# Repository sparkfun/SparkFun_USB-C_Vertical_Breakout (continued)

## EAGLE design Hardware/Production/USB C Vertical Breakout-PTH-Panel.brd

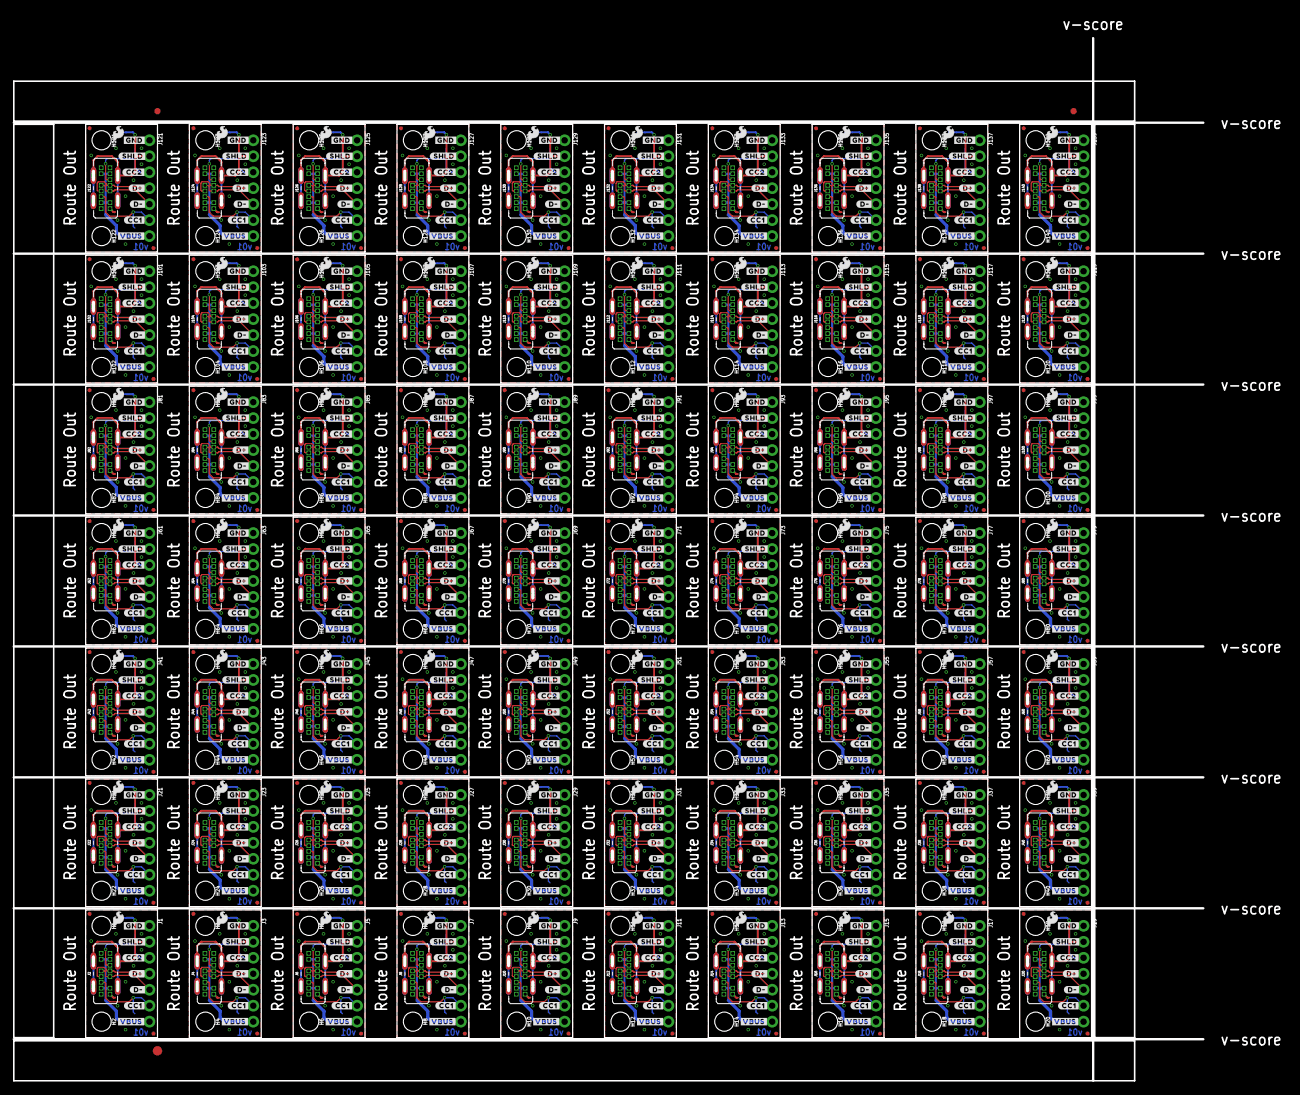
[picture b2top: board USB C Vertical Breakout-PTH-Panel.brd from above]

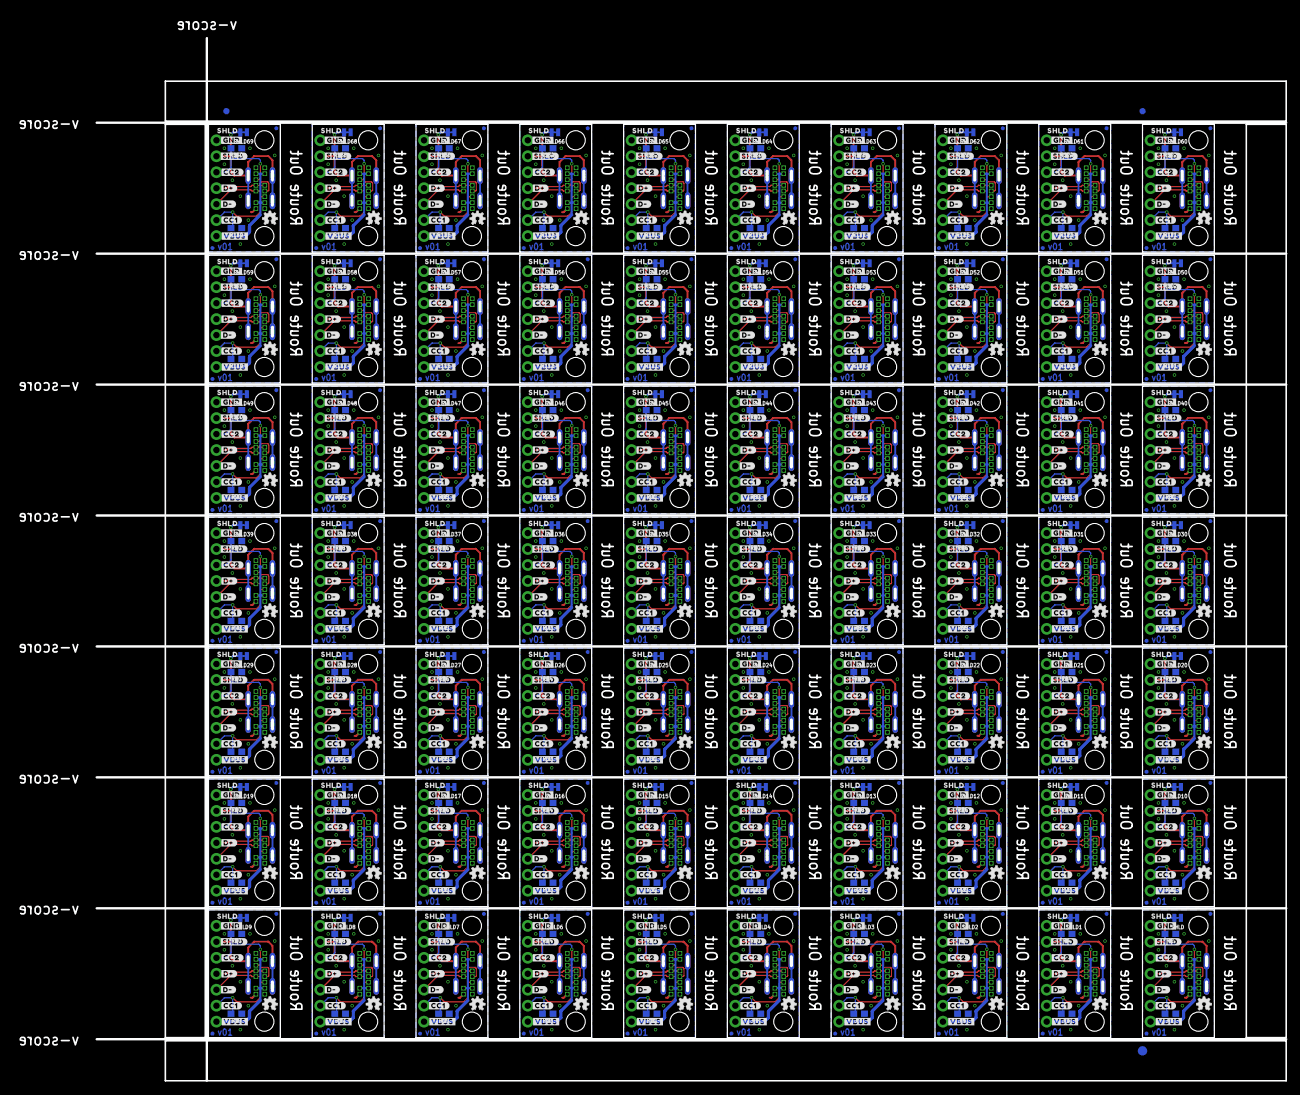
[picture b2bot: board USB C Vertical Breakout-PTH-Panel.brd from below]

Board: 2 copper layers, 189.2 x 165.9 mm, 2036 parts (983 on the bottom side), 490 nets.

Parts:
E$1, E$2, E$3, E$4: FIDUCIAL-1X2
E$5, E$6: FIDUCIAL-1.5X3
FD1, FD2, FD3, FD4, FD5, FD6, FD7, FD8, FD9, FD10, FD11, FD12, FD13, FD14, FD15, FD16, FD17, FD18, FD19, FD20, FD21, FD22, FD23, FD24, FD25, FD26, FD27, FD28, FD29, FD30, FD31, FD32, FD33, FD34, FD35, FD36, FD37, FD38, FD39, FD40, FD41, FD42, FD43, FD44, FD45, FD46, FD47, FD48, FD49, FD50, FD51, FD52, FD53, FD54, FD55, FD56, FD57, FD58, FD59, FD60, FD61, FD62, FD63, FD64, FD65, FD66, FD67, FD68, FD69, FD70, FD71, FD72, FD73, FD74, FD75, FD76, FD77, FD78, FD79, FD80, FD81, FD82, FD83, FD84, FD85, FD86, FD87, FD88, FD89, FD90, FD91, FD92, FD93, FD94, FD95, FD96, FD97, FD98, FD99, FD100, FD101, FD102, FD103, FD104, FD105, FD106, FD107, FD108, FD109, FD110, FD111, FD112, FD113, FD114, FD115, FD116, FD117, FD118, FD119, FD120, FD121, FD122, FD123, FD124, FD125, FD126, FD127, FD128, FD129, FD130, FD131, FD132, FD133, FD134, FD135, FD136, FD137, FD138, FD139, FD140, FD141, FD142, FD143, FD144, FD145, FD146, FD147, FD148, FD149, FD150, FD151, FD152, FD153, FD154, FD155, FD156, FD157, FD158, FD159, FD160, FD161, FD162, FD163, FD164, FD165, FD166, FD167, FD168, FD169, FD170, FD171, FD172, FD173, FD174, FD175, FD176, FD177, FD178, FD179, FD180, FD181, FD182, FD183, FD184, FD185, FD186, FD187, FD188, FD189, FD190, FD191, FD192, FD193, FD194, FD195, FD196, FD197, FD198, FD199, FD200, FD201, FD202, FD203, FD204, FD205, FD206, FD207, FD208, FD209, FD210, FD211, FD212, FD213, FD214, FD215, FD216, FD217, FD218, FD219, FD220, FD221, FD222, FD223, FD224, FD225, FD226, FD227, FD228, FD229, FD230, FD231, FD232, FD233, FD234, FD235, FD236, FD237, FD238, FD239, FD240, FD241, FD242, FD243, FD244, FD245, FD246, FD247, FD248, FD249, FD250, FD251, FD252, FD253, FD254, FD255, FD256, FD257, FD258, FD259, FD260, FD261, FD262, FD263, FD264, FD265, FD266, FD267, FD268, FD269, FD270, FD271, FD272, FD273, FD274, FD275, FD276, FD277, FD278, FD279, FD280: FIDUCIALUFIDUCIAL; FIDUCIAL-MICRO
H1, H2, H3, H4, H5, H6, H7, H8, H9, H10, H11, H12, H13, H14, H15, H16, H17, H18, H19, H20, H21, H22, H23, H24, H25, H26, H27, H28, H29, H30, H31, H32, H33, H34, H35, H36, H37, H38, H39, H40, H41, H42, H43, H44, H45, H46, H47, H48, H49, H50, H51, H52, H53, H54, H55, H56, H57, H58, H59, H60, H61, H62, H63, H64, H65, H66, H67, H68, H69, H70, H71, H72, H73, H74, H75, H76, H77, H78, H79, H80, H81, H82, H83, H84, H85, H86, H87, H88, H89, H90, H91, H92, H93, H94, H95, H96, H97, H98, H99, H100, H101, H102, H103, H104, H105, H106, H107, H108, H109, H110, H111, H112, H113, H114, H115, H116, H117, H118, H119, H120, H121, H122, H123, H124, H125, H126, H127, H128, H129, H130, H131, H132, H133, H134, H135, H136, H137, H138, H139, H140: STAND-OFFTIGHT; STAND-OFF-TIGHT
J1, J3, J5, J7, J9, J11, J13, J15, J17, J19, J21, J23, J25, J27, J29, J31, J33, J35, J37, J39, J41, J43, J45, J47, J49, J51, J53, J55, J57, J59, J61, J63, J65, J67, J69, J71, J73, J75, J77, J79, J81, J83, J85, J87, J89, J91, J93, J95, J97, J99, J101, J103, J105, J107, J109, J111, J113, J115, J117, J119, J121, J123, J125, J127, J129, J131, J133, J135, J137, J139: 1X07_NO_SILK
J2, J4, J6, J8, J10, J12, J14, J16, J18, J20, J22, J24, J26, J28, J30, J32, J34, J36, J38, J40, J42, J44, J46, J48, J50, J52, J54, J56, J58, J60, J62, J64, J66, J68, J70, J72, J74, J76, J78, J80, J82, J84, J86, J88, J90, J92, J94, J96, J98, J100, J102, J104, J106, J108, J110, J112, J114, J116, J118, J120, J122, J124, J126, J128, J130, J132, J134, J136, J138, J140: USB-C-8P-2LAYER-VERTICAL-PTH
LOGO1, LOGO5, LOGO8, LOGO11, LOGO14, LOGO17, LOGO20, LOGO23, LOGO26, LOGO29, LOGO32, LOGO35, LOGO38, LOGO41, LOGO44, LOGO47, LOGO50, LOGO53, LOGO56, LOGO59, LOGO62, LOGO65, LOGO68, LOGO71, LOGO74, LOGO77, LOGO80, LOGO83, LOGO86, LOGO89, LOGO92, LOGO95, LOGO98, LOGO101, LOGO104, LOGO107, LOGO110, LOGO113, LOGO116, LOGO119, LOGO122, LOGO125, LOGO128, LOGO131, LOGO134, LOGO137, LOGO140, LOGO143, LOGO146, LOGO149, LOGO152, LOGO155, LOGO158, LOGO161, LOGO164, LOGO167, LOGO170, LOGO173, LOGO176, LOGO179, LOGO182, LOGO185, LOGO188, LOGO191, LOGO194, LOGO197, LOGO200, LOGO203, LOGO206, LOGO209: SFE_LOGO_NAME_FLAMEBLANK; BLANK
LOGO2, LOGO4, LOGO7, LOGO10, LOGO13, LOGO16, LOGO19, LOGO22, LOGO25, LOGO28, LOGO31, LOGO34, LOGO37, LOGO40, LOGO43, LOGO46, LOGO49, LOGO52, LOGO55, LOGO58, LOGO61, LOGO64, LOGO67, LOGO70, LOGO73, LOGO76, LOGO79, LOGO82, LOGO85, LOGO88, LOGO91, LOGO94, LOGO97, LOGO100, LOGO103, LOGO106, LOGO109, LOGO112, LOGO115, LOGO118, LOGO121, LOGO124, LOGO127, LOGO130, LOGO133, LOGO136, LOGO139, LOGO142, LOGO145, LOGO148, LOGO151, LOGO154, LOGO157, LOGO160, LOGO163, LOGO166, LOGO169, LOGO172, LOGO175, LOGO178, LOGO181, LOGO184, LOGO187, LOGO190, LOGO193, LOGO196, LOGO199, LOGO202, LOGO205, LOGO208: OSHW-LOGOMINI; OSHW-LOGO-MINI
LOGO3, LOGO6, LOGO9, LOGO12, LOGO15, LOGO18, LOGO21, LOGO24, LOGO27, LOGO30, LOGO33, LOGO36, LOGO39, LOGO42, LOGO45, LOGO48, LOGO51, LOGO54, LOGO57, LOGO60, LOGO63, LOGO66, LOGO69, LOGO72, LOGO75, LOGO78, LOGO81, LOGO84, LOGO87, LOGO90, LOGO93, LOGO96, LOGO99, LOGO102, LOGO105, LOGO108, LOGO111, LOGO114, LOGO117, LOGO120, LOGO123, LOGO126, LOGO129, LOGO132, LOGO135, LOGO138, LOGO141, LOGO144, LOGO147, LOGO150, LOGO153, LOGO156, LOGO159, LOGO162, LOGO165, LOGO168, LOGO171, LOGO174, LOGO177, LOGO180, LOGO183, LOGO186, LOGO189, LOGO192, LOGO195, LOGO198, LOGO201, LOGO204, LOGO207, LOGO210: SFE_LOGO_FLAME.1_INCH; SFE_LOGO_FLAME_.1
R1, R2, R3, R4, R5, R6, R7, R8, R9, R10, R11, R12, R13, R14, R15, R16, R17, R18, R19, R20, R21, R22, R23, R24, R25, R26, R27, R28, R29, R30, R31, R32, R33, R34, R35, R36, R37, R38, R39, R40, R41, R42, R43, R44, R45, R46, R47, R48, R49, R50, R51, R52, R53, R54, R55, R56, R57, R58, R59, R60, R61, R62, R63, R64, R65, R66, R67, R68, R69, R70, R71, R72, R73, R74, R75, R76, R77, R78, R79, R80, R81, R82, R83, R84, R85, R86, R87, R88, R89, R90, R91, R92, R93, R94, R95, R96, R97, R98, R99, R100, R101, R102, R103, R104, R105, R106, R107, R108, R109, R110, R111, R112, R113, R114, R115, R116, R117, R118, R119, R120, R121, R122, R123, R124, R125, R126, R127, R128, R129, R130, R131, R132, R133, R134, R135, R136, R137, R138, R139, R140: 5.1k; 0603
SHLD, SHLD1, SHLD2, SHLD3, SHLD4, SHLD5, SHLD6, SHLD7, SHLD8, SHLD9, SHLD10, SHLD11, SHLD12, SHLD13, SHLD14, SHLD15, SHLD16, SHLD17, SHLD18, SHLD19, SHLD20, SHLD21, SHLD22, SHLD23, SHLD24, SHLD25, SHLD26, SHLD27, SHLD28, SHLD29, SHLD30, SHLD31, SHLD32, SHLD33, SHLD34, SHLD35, SHLD36, SHLD37, SHLD38, SHLD39, SHLD40, SHLD41, SHLD42, SHLD43, SHLD44, SHLD45, SHLD46, SHLD47, SHLD48, SHLD49, SHLD50, SHLD51, SHLD52, SHLD53, SHLD54, SHLD55, SHLD56, SHLD57, SHLD58, SHLD59, SHLD60, SHLD61, SHLD62, SHLD63, SHLD64, SHLD65, SHLD66, SHLD67, SHLD68, SHLD69: SHLD; SMT-JUMPER_2_NC_TRACE_NO-SILK
U$1, U$30, U$45, U$60, U$75, U$90, U$105, U$120, U$135, U$150, U$165, U$180, U$195, U$210, U$225, U$240, U$255, U$270, U$285, U$300, U$315, U$330, U$345, U$360, U$375, U$390, U$405, U$420, U$435, U$450, U$465, U$480, U$495, U$510, U$525, U$540, U$555, U$570, U$585, U$600, U$615, U$630, U$645, U$660, U$675, U$690, U$705, U$720, U$735, U$750, U$765, U$780, U$795, U$810, U$825, U$840, U$855, U$870, U$885, U$900, U$915, U$930, U$945, U$960, U$975, U$990, U$1005, U$1020, U$1035, U$1050: SHLD0
U$2, U$16, U$31, U$46, U$61, U$76, U$91, U$106, U$121, U$136, U$151, U$166, U$181, U$196, U$211, U$226, U$241, U$256, U$271, U$286, U$301, U$316, U$331, U$346, U$361, U$376, U$391, U$406, U$421, U$436, U$451, U$466, U$481, U$496, U$511, U$526, U$541, U$556, U$571, U$586, U$601, U$616, U$631, U$646, U$661, U$676, U$691, U$706, U$721, U$736, U$751, U$766, U$781, U$796, U$811, U$826, U$841, U$856, U$871, U$886, U$901, U$916, U$931, U$946, U$961, U$976, U$991, U$1006, U$1021, U$1036: #CC2#0
U$3, U$4, U$32, U$47, U$62, U$77, U$92, U$107, U$122, U$137, U$152, U$167, U$182, U$197, U$212, U$227, U$242, U$257, U$272, U$287, U$302, U$317, U$332, U$347, U$362, U$377, U$392, U$407, U$422, U$437, U$452, U$467, U$482, U$497, U$512, U$527, U$542, U$557, U$572, U$587, U$602, U$617, U$632, U$647, U$662, U$677, U$692, U$707, U$722, U$737, U$752, U$767, U$782, U$797, U$812, U$827, U$842, U$857, U$872, U$887, U$902, U$917, U$932, U$947, U$962, U$977, U$992, U$1007, U$1022, U$1037: #D##3
U$5, U$7, U$33, U$48, U$63, U$78, U$93, U$108, U$123, U$138, U$153, U$168, U$183, U$198, U$213, U$228, U$243, U$258, U$273, U$288, U$303, U$318, U$333, U$348, U$363, U$378, U$393, U$408, U$423, U$438, U$453, U$468, U$483, U$498, U$513, U$528, U$543, U$558, U$573, U$588, U$603, U$618, U$633, U$648, U$663, U$678, U$693, U$708, U$723, U$738, U$753, U$768, U$783, U$798, U$813, U$828, U$843, U$858, U$873, U$888, U$903, U$918, U$933, U$948, U$963, U$978, U$993, U$1008, U$1023, U$1038: #D##4
U$6, U$17, U$34, U$49, U$64, U$79, U$94, U$109, U$124, U$139, U$154, U$169, U$184, U$199, U$214, U$229, U$244, U$259, U$274, U$289, U$304, U$319, U$334, U$349, U$364, U$379, U$394, U$409, U$424, U$439, U$454, U$469, U$484, U$499, U$514, U$529, U$544, U$559, U$574, U$589, U$604, U$619, U$634, U$649, U$664, U$679, U$694, U$709, U$724, U$739, U$754, U$769, U$784, U$799, U$814, U$829, U$844, U$859, U$874, U$889, U$904, U$919, U$934, U$949, U$964, U$979, U$994, U$1009, U$1024, U$1039: #CC1#5
U$8, U$18, U$35, U$50, U$65, U$80, U$95, U$110, U$125, U$140, U$155, U$170, U$185, U$200, U$215, U$230, U$245, U$260, U$275, U$290, U$305, U$320, U$335, U$350, U$365, U$380, U$395, U$410, U$425, U$440, U$455, U$470, U$485, U$500, U$515, U$530, U$545, U$560, U$575, U$590, U$605, U$620, U$635, U$650, U$665, U$680, U$695, U$710, U$725, U$740, U$755, U$770, U$785, U$800, U$815, U$830, U$845, U$860, U$875, U$890, U$905, U$920, U$935, U$950, U$965, U$980, U$995, U$1010, U$1025, U$1040: #SHLD#5
U$9, U$10, U$13, U$21, U$36, U$39, U$51, U$54, U$66, U$69, U$81, U$84, U$96, U$99, U$111, U$114, U$126, U$129, U$141, U$144, U$156, U$159, U$171, U$174, U$186, U$189, U$201, U$204, U$216, U$219, U$231, U$234, U$246, U$249, U$261, U$264, U$276, U$279, U$291, U$294, U$306, U$309, U$321, U$324, U$336, U$339, U$351, U$354, U$366, U$369, U$381, U$384, U$396, U$399, U$411, U$414, U$426, U$429, U$441, U$444, U$456, U$459, U$471, U$474, U$486, U$489, U$501, U$504, U$516, U$519, U$531, U$534, U$546, U$549, U$561, U$564, U$576, U$579, U$591, U$594, U$606, U$609, U$621, U$624, U$636, U$639, U$651, U$654, U$666, U$669, U$681, U$684, U$696, U$699, U$711, U$714, U$726, U$729, U$741, U$744, U$756, U$759, U$771, U$774, U$786, U$789, U$801, U$804, U$816, U$819, U$831, U$834, U$846, U$849, U$861, U$864, U$876, U$879, U$891, U$894, U$906, U$909, U$921, U$924, U$936, U$939, U$951, U$954, U$966, U$969, U$981, U$984, U$996, U$999, U$1011, U$1014, U$1026, U$1029, U$1041, U$1044: #GND#6
U$11, U$12, U$19, U$20, U$37, U$38, U$52, U$53, U$67, U$68, U$82, U$83, U$97, U$98, U$112, U$113, U$127, U$128, U$142, U$143, U$157, U$158, U$172, U$173, U$187, U$188, U$202, U$203, U$217, U$218, U$232, U$233, U$247, U$248, U$262, U$263, U$277, U$278, U$292, U$293, U$307, U$308, U$322, U$323, U$337, U$338, U$352, U$353, U$367, U$368, U$382, U$383, U$397, U$398, U$412, U$413, U$427, U$428, U$442, U$443, U$457, U$458, U$472, U$473, U$487, U$488, U$502, U$503, U$517, U$518, U$532, U$533, U$547, U$548, U$562, U$563, U$577, U$578, U$592, U$593, U$607, U$608, U$622, U$623, U$637, U$638, U$652, U$653, U$667, U$668, U$682, U$683, U$697, U$698, U$712, U$713, U$727, U$728, U$742, U$743, U$757, U$758, U$772, U$773, U$787, U$788, U$802, U$803, U$817, U$818, U$832, U$833, U$847, U$848, U$862, U$863, U$877, U$878, U$892, U$893, U$907, U$908, U$922, U$923, U$937, U$938, U$952, U$953, U$967, U$968, U$982, U$983, U$997, U$998, U$1012, U$1013, U$1027, U$1028, U$1042, U$1043: #VBUS#7
U$14, U$22, U$40, U$55, U$70, U$85, U$100, U$115, U$130, U$145, U$160, U$175, U$190, U$205, U$220, U$235, U$250, U$265, U$280, U$295, U$310, U$325, U$340, U$355, U$370, U$385, U$400, U$415, U$430, U$445, U$460, U$475, U$490, U$505, U$520, U$535, U$550, U$565, U$580, U$595, U$610, U$625, U$640, U$655, U$670, U$685, U$700, U$715, U$730, U$745, U$760, U$775, U$790, U$805, U$820, U$835, U$850, U$865, U$880, U$895, U$910, U$925, U$940, U$955, U$970, U$985, U$1000, U$1015, U$1030, U$1045: #SHLD#8
U$15, U$23, U$41, U$56, U$71, U$86, U$101, U$116, U$131, U$146, U$161, U$176, U$191, U$206, U$221, U$236, U$251, U$266, U$281, U$296, U$311, U$326, U$341, U$356, U$371, U$386, U$401, U$416, U$431, U$446, U$461, U$476, U$491, U$506, U$521, U$536, U$551, U$566, U$581, U$596, U$611, U$626, U$641, U$656, U$671, U$686, U$701, U$716, U$731, U$746, U$761, U$776, U$791, U$806, U$821, U$836, U$851, U$866, U$881, U$896, U$911, U$926, U$941, U$956, U$971, U$986, U$1001, U$1016, U$1031, U$1046: #CC2#9
U$24, U$27, U$42, U$57, U$72, U$87, U$102, U$117, U$132, U$147, U$162, U$177, U$192, U$207, U$222, U$237, U$252, U$267, U$282, U$297, U$312, U$327, U$342, U$357, U$372, U$387, U$402, U$417, U$432, U$447, U$462, U$477, U$492, U$507, U$522, U$537, U$552, U$567, U$582, U$597, U$612, U$627, U$642, U$657, U$672, U$687, U$702, U$717, U$732, U$747, U$762, U$777, U$792, U$807, U$822, U$837, U$852, U$867, U$882, U$897, U$912, U$927, U$942, U$957, U$972, U$987, U$1002, U$1017, U$1032, U$1047: #D##9
U$25, U$28, U$43, U$58, U$73, U$88, U$103, U$118, U$133, U$148, U$163, U$178, U$193, U$208, U$223, U$238, U$253, U$268, U$283, U$298, U$313, U$328, U$343, U$358, U$373, U$388, U$403, U$418, U$433, U$448, U$463, U$478, U$493, U$508, U$523, U$538, U$553, U$568, U$583, U$598, U$613, U$628, U$643, U$658, U$673, U$688, U$703, U$718, U$733, U$748, U$763, U$778, U$793, U$808, U$823, U$838, U$853, U$868, U$883, U$898, U$913, U$928, U$943, U$958, U$973, U$988, U$1003, U$1018, U$1033, U$1048: #D##10
U$26, U$29, U$44, U$59, U$74, U$89, U$104, U$119, U$134, U$149, U$164, U$179, U$194, U$209, U$224, U$239, U$254, U$269, U$284, U$299, U$314, U$329, U$344, U$359, U$374, U$389, U$404, U$419, U$434, U$449, U$464, U$479, U$494, U$509, U$524, U$539, U$554, U$569, U$584, U$599, U$614, U$629, U$644, U$659, U$674, U$689, U$704, U$719, U$734, U$749, U$764, U$779, U$794, U$809, U$824, U$839, U$854, U$869, U$884, U$899, U$914, U$929, U$944, U$959, U$974, U$989, U$1004, U$1019, U$1034, U$1049: #CC1#11

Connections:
CC1: J1.6, J2.A5, R1.2
CC2: J1.3, J2.B5, R2.2
CC3: J3.6, J4.A5, R3.2
CC4: J3.3, J4.B5, R4.2
CC5: J5.6, J6.A5, R5.2
CC6: J5.3, J6.B5, R6.2
CC7: J7.6, J8.A5, R7.2
CC8: J7.3, J8.B5, R8.2
CC9: J9.6, J10.A5, R9.2
CC10: J9.3, J10.B5, R10.2
CC11: J11.6, J12.A5, R11.2
CC12: J11.3, J12.B5, R12.2
CC13: J13.6, J14.A5, R13.2
CC14: J13.3, J14.B5, R14.2
CC15: J15.6, J16.A5, R15.2
CC16: J15.3, J16.B5, R16.2
CC17: J17.6, J18.A5, R17.2
CC18: J17.3, J18.B5, R18.2
CC19: J19.6, J20.A5, R19.2
CC20: J19.3, J20.B5, R20.2
CC21: J21.6, J22.A5, R21.2
CC22: J21.3, J22.B5, R22.2
CC23: J23.6, J24.A5, R23.2
CC24: J23.3, J24.B5, R24.2
CC25: J25.6, J26.A5, R25.2
CC26: J25.3, J26.B5, R26.2
CC27: J27.6, J28.A5, R27.2
CC28: J27.3, J28.B5, R28.2
CC29: J29.6, J30.A5, R29.2
CC30: J29.3, J30.B5, R30.2
CC31: J31.6, J32.A5, R31.2
CC32: J31.3, J32.B5, R32.2
CC33: J33.6, J34.A5, R33.2
CC34: J33.3, J34.B5, R34.2
CC35: J35.6, J36.A5, R35.2
CC36: J35.3, J36.B5, R36.2
CC37: J37.6, J38.A5, R37.2
CC38: J37.3, J38.B5, R38.2
CC39: J39.6, J40.A5, R39.2
CC40: J39.3, J40.B5, R40.2
CC41: J41.6, J42.A5, R41.2
CC42: J41.3, J42.B5, R42.2
CC43: J43.6, J44.A5, R43.2
CC44: J43.3, J44.B5, R44.2
CC45: J45.6, J46.A5, R45.2
CC46: J45.3, J46.B5, R46.2
CC47: J47.6, J48.A5, R47.2
CC48: J47.3, J48.B5, R48.2
CC49: J49.6, J50.A5, R49.2
CC50: J49.3, J50.B5, R50.2
CC51: J51.6, J52.A5, R51.2
CC52: J51.3, J52.B5, R52.2
CC53: J53.6, J54.A5, R53.2
CC54: J53.3, J54.B5, R54.2
CC55: J55.6, J56.A5, R55.2
CC56: J55.3, J56.B5, R56.2
CC57: J57.6, J58.A5, R57.2
CC58: J57.3, J58.B5, R58.2
CC59: J59.6, J60.A5, R59.2
CC60: J59.3, J60.B5, R60.2
CC61: J61.6, J62.A5, R61.2
CC62: J61.3, J62.B5, R62.2
CC63: J63.6, J64.A5, R63.2
CC64: J63.3, J64.B5, R64.2
CC65: J65.6, J66.A5, R65.2
CC66: J65.3, J66.B5, R66.2
CC67: J67.6, J68.A5, R67.2
CC68: J67.3, J68.B5, R68.2
CC69: J69.6, J70.A5, R69.2
CC70: J69.3, J70.B5, R70.2
CC71: J71.6, J72.A5, R71.2
CC72: J71.3, J72.B5, R72.2
CC73: J73.6, J74.A5, R73.2
CC74: J73.3, J74.B5, R74.2
CC75: J75.6, J76.A5, R75.2
CC76: J75.3, J76.B5, R76.2
CC77: J77.6, J78.A5, R77.2
CC78: J77.3, J78.B5, R78.2
CC79: J79.6, J80.A5, R79.2
CC80: J79.3, J80.B5, R80.2
CC81: J81.6, J82.A5, R81.2
CC82: J81.3, J82.B5, R82.2
CC83: J83.6, J84.A5, R83.2
CC84: J83.3, J84.B5, R84.2
CC85: J85.6, J86.A5, R85.2
CC86: J85.3, J86.B5, R86.2
CC87: J87.6, J88.A5, R87.2
CC88: J87.3, J88.B5, R88.2
CC89: J89.6, J90.A5, R89.2
CC90: J89.3, J90.B5, R90.2
CC91: J91.6, J92.A5, R91.2
CC92: J91.3, J92.B5, R92.2
CC93: J93.6, J94.A5, R93.2
CC94: J93.3, J94.B5, R94.2
CC95: J95.6, J96.A5, R95.2
CC96: J95.3, J96.B5, R96.2
CC97: J97.6, J98.A5, R97.2
CC98: J97.3, J98.B5, R98.2
CC99: J99.6, J100.A5, R99.2
CC100: J99.3, J100.B5, R100.2
CC101: J101.6, J102.A5, R101.2
CC102: J101.3, J102.B5, R102.2
CC103: J103.6, J104.A5, R103.2
CC104: J103.3, J104.B5, R104.2
CC105: J105.6, J106.A5, R105.2
CC106: J105.3, J106.B5, R106.2
CC107: J107.6, J108.A5, R107.2
CC108: J107.3, J108.B5, R108.2
CC109: J109.6, J110.A5, R109.2
CC110: J109.3, J110.B5, R110.2
CC111: J111.6, J112.A5, R111.2
CC112: J111.3, J112.B5, R112.2
CC113: J113.6, J114.A5, R113.2
CC114: J113.3, J114.B5, R114.2
CC115: J115.6, J116.A5, R115.2
CC116: J115.3, J116.B5, R116.2
CC117: J117.6, J118.A5, R117.2
CC118: J117.3, J118.B5, R118.2
CC119: J119.6, J120.A5, R119.2
CC120: J119.3, J120.B5, R120.2
CC121: J121.6, J122.A5, R121.2
CC122: J121.3, J122.B5, R122.2
CC123: J123.6, J124.A5, R123.2
CC124: J123.3, J124.B5, R124.2
CC125: J125.6, J126.A5, R125.2
CC126: J125.3, J126.B5, R126.2
CC127: J127.6, J128.A5, R127.2
CC128: J127.3, J128.B5, R128.2
CC129: J129.6, J130.A5, R129.2
CC130: J129.3, J130.B5, R130.2
CC131: J131.6, J132.A5, R131.2
CC132: J131.3, J132.B5, R132.2
CC133: J133.6, J134.A5, R133.2
CC134: J133.3, J134.B5, R134.2
CC135: J135.6, J136.A5, R135.2
CC136: J135.3, J136.B5, R136.2
CC137: J137.6, J138.A5, R137.2
CC138: J137.3, J138.B5, R138.2
CC139: J139.6, J140.A5, R139.2
CC140: J139.3, J140.B5, R140.2
D+: J1.4, J2.A6, J2.B6
D+1: J3.4, J4.A6, J4.B6
D+2: J5.4, J6.A6, J6.B6
D+3: J7.4, J8.A6, J8.B6
D+4: J9.4, J10.A6, J10.B6
D+5: J11.4, J12.A6, J12.B6
D+6: J13.4, J14.A6, J14.B6
D+7: J15.4, J16.A6, J16.B6
D+8: J17.4, J18.A6, J18.B6
D+9: J19.4, J20.A6, J20.B6
D+10: J21.4, J22.A6, J22.B6
D+11: J23.4, J24.A6, J24.B6
D+12: J25.4, J26.A6, J26.B6
D+13: J27.4, J28.A6, J28.B6
D+14: J29.4, J30.A6, J30.B6
D+15: J31.4, J32.A6, J32.B6
D+16: J33.4, J34.A6, J34.B6
D+17: J35.4, J36.A6, J36.B6
D+18: J37.4, J38.A6, J38.B6
D+19: J39.4, J40.A6, J40.B6
D+20: J41.4, J42.A6, J42.B6
D+21: J43.4, J44.A6, J44.B6
D+22: J45.4, J46.A6, J46.B6
D+23: J47.4, J48.A6, J48.B6
D+24: J49.4, J50.A6, J50.B6
D+25: J51.4, J52.A6, J52.B6
D+26: J53.4, J54.A6, J54.B6
D+27: J55.4, J56.A6, J56.B6
D+28: J57.4, J58.A6, J58.B6
D+29: J59.4, J60.A6, J60.B6
D+30: J61.4, J62.A6, J62.B6
D+31: J63.4, J64.A6, J64.B6
D+32: J65.4, J66.A6, J66.B6
D+33: J67.4, J68.A6, J68.B6
D+34: J69.4, J70.A6, J70.B6
D+35: J71.4, J72.A6, J72.B6
D+36: J73.4, J74.A6, J74.B6
D+37: J75.4, J76.A6, J76.B6
D+38: J77.4, J78.A6, J78.B6
D+39: J79.4, J80.A6, J80.B6
D+40: J81.4, J82.A6, J82.B6
D+41: J83.4, J84.A6, J84.B6
D+42: J85.4, J86.A6, J86.B6
D+43: J87.4, J88.A6, J88.B6
D+44: J89.4, J90.A6, J90.B6
D+45: J91.4, J92.A6, J92.B6
D+46: J93.4, J94.A6, J94.B6
D+47: J95.4, J96.A6, J96.B6
D+48: J97.4, J98.A6, J98.B6
D+49: J99.4, J100.A6, J100.B6
D+50: J101.4, J102.A6, J102.B6
D+51: J103.4, J104.A6, J104.B6
D+52: J105.4, J106.A6, J106.B6
D+53: J107.4, J108.A6, J108.B6
D+54: J109.4, J110.A6, J110.B6
D+55: J111.4, J112.A6, J112.B6
D+56: J113.4, J114.A6, J114.B6
D+57: J115.4, J116.A6, J116.B6
D+58: J117.4, J118.A6, J118.B6
D+59: J119.4, J120.A6, J120.B6
D+60: J121.4, J122.A6, J122.B6
D+61: J123.4, J124.A6, J124.B6
D+62: J125.4, J126.A6, J126.B6
D+63: J127.4, J128.A6, J128.B6
D+64: J129.4, J130.A6, J130.B6
D+65: J131.4, J132.A6, J132.B6
D+66: J133.4, J134.A6, J134.B6
D+67: J135.4, J136.A6, J136.B6
D+68: J137.4, J138.A6, J138.B6
D+69: J139.4, J140.A6, J140.B6
D-: J1.5, J2.A7, J2.B7
D-1: J3.5, J4.A7, J4.B7
D-2: J5.5, J6.A7, J6.B7
D-3: J7.5, J8.A7, J8.B7
D-4: J9.5, J10.A7, J10.B7
D-5: J11.5, J12.A7, J12.B7
D-6: J13.5, J14.A7, J14.B7
D-7: J15.5, J16.A7, J16.B7
D-8: J17.5, J18.A7, J18.B7
D-9: J19.5, J20.A7, J20.B7
D-10: J21.5, J22.A7, J22.B7
D-11: J23.5, J24.A7, J24.B7
D-12: J25.5, J26.A7, J26.B7
D-13: J27.5, J28.A7, J28.B7
D-14: J29.5, J30.A7, J30.B7
D-15: J31.5, J32.A7, J32.B7
D-16: J33.5, J34.A7, J34.B7
D-17: J35.5, J36.A7, J36.B7
D-18: J37.5, J38.A7, J38.B7
D-19: J39.5, J40.A7, J40.B7
D-20: J41.5, J42.A7, J42.B7
D-21: J43.5, J44.A7, J44.B7
D-22: J45.5, J46.A7, J46.B7
D-23: J47.5, J48.A7, J48.B7
D-24: J49.5, J50.A7, J50.B7
D-25: J51.5, J52.A7, J52.B7
D-26: J53.5, J54.A7, J54.B7
D-27: J55.5, J56.A7, J56.B7
D-28: J57.5, J58.A7, J58.B7
D-29: J59.5, J60.A7, J60.B7
D-30: J61.5, J62.A7, J62.B7
D-31: J63.5, J64.A7, J64.B7
D-32: J65.5, J66.A7, J66.B7
D-33: J67.5, J68.A7, J68.B7
D-34: J69.5, J70.A7, J70.B7
D-35: J71.5, J72.A7, J72.B7
D-36: J73.5, J74.A7, J74.B7
D-37: J75.5, J76.A7, J76.B7
D-38: J77.5, J78.A7, J78.B7
D-39: J79.5, J80.A7, J80.B7
D-40: J81.5, J82.A7, J82.B7
D-41: J83.5, J84.A7, J84.B7
D-42: J85.5, J86.A7, J86.B7
D-43: J87.5, J88.A7, J88.B7
D-44: J89.5, J90.A7, J90.B7
D-45: J91.5, J92.A7, J92.B7
D-46: J93.5, J94.A7, J94.B7
D-47: J95.5, J96.A7, J96.B7
D-48: J97.5, J98.A7, J98.B7
D-49: J99.5, J100.A7, J100.B7
D-50: J101.5, J102.A7, J102.B7
D-51: J103.5, J104.A7, J104.B7
D-52: J105.5, J106.A7, J106.B7
D-53: J107.5, J108.A7, J108.B7
D-54: J109.5, J110.A7, J110.B7
D-55: J111.5, J112.A7, J112.B7
D-56: J113.5, J114.A7, J114.B7
D-57: J115.5, J116.A7, J116.B7
D-58: J117.5, J118.A7, J118.B7
D-59: J119.5, J120.A7, J120.B7
D-60: J121.5, J122.A7, J122.B7
D-61: J123.5, J124.A7, J124.B7
D-62: J125.5, J126.A7, J126.B7
D-63: J127.5, J128.A7, J128.B7
D-64: J129.5, J130.A7, J130.B7
D-65: J131.5, J132.A7, J132.B7
D-66: J133.5, J134.A7, J134.B7
D-67: J135.5, J136.A7, J136.B7
D-68: J137.5, J138.A7, J138.B7
D-69: J139.5, J140.A7, J140.B7
GND: J1.1, J2.A1, J2.A12, J2.B1, J2.B12, R1.1, R2.1, SHLD.1
GND1: J3.1, J4.A1, J4.A12, J4.B1, J4.B12, R3.1, R4.1, SHLD1.1
GND2: J5.1, J6.A1, J6.A12, J6.B1, J6.B12, R5.1, R6.1, SHLD2.1
GND3: J7.1, J8.A1, J8.A12, J8.B1, J8.B12, R7.1, R8.1, SHLD3.1
GND4: J9.1, J10.A1, J10.A12, J10.B1, J10.B12, R9.1, R10.1, SHLD4.1
GND5: J11.1, J12.A1, J12.A12, J12.B1, J12.B12, R11.1, R12.1, SHLD5.1
GND6: J13.1, J14.A1, J14.A12, J14.B1, J14.B12, R13.1, R14.1, SHLD6.1
GND7: J15.1, J16.A1, J16.A12, J16.B1, J16.B12, R15.1, R16.1, SHLD7.1
GND8: J17.1, J18.A1, J18.A12, J18.B1, J18.B12, R17.1, R18.1, SHLD8.1
GND9: J19.1, J20.A1, J20.A12, J20.B1, J20.B12, R19.1, R20.1, SHLD9.1
GND10: J21.1, J22.A1, J22.A12, J22.B1, J22.B12, R21.1, R22.1, SHLD10.1
GND11: J23.1, J24.A1, J24.A12, J24.B1, J24.B12, R23.1, R24.1, SHLD11.1
GND12: J25.1, J26.A1, J26.A12, J26.B1, J26.B12, R25.1, R26.1, SHLD12.1
GND13: J27.1, J28.A1, J28.A12, J28.B1, J28.B12, R27.1, R28.1, SHLD13.1
GND14: J29.1, J30.A1, J30.A12, J30.B1, J30.B12, R29.1, R30.1, SHLD14.1
GND15: J31.1, J32.A1, J32.A12, J32.B1, J32.B12, R31.1, R32.1, SHLD15.1
GND16: J33.1, J34.A1, J34.A12, J34.B1, J34.B12, R33.1, R34.1, SHLD16.1
GND17: J35.1, J36.A1, J36.A12, J36.B1, J36.B12, R35.1, R36.1, SHLD17.1
GND18: J37.1, J38.A1, J38.A12, J38.B1, J38.B12, R37.1, R38.1, SHLD18.1
GND19: J39.1, J40.A1, J40.A12, J40.B1, J40.B12, R39.1, R40.1, SHLD19.1
GND20: J41.1, J42.A1, J42.A12, J42.B1, J42.B12, R41.1, R42.1, SHLD20.1
GND21: J43.1, J44.A1, J44.A12, J44.B1, J44.B12, R43.1, R44.1, SHLD21.1
GND22: J45.1, J46.A1, J46.A12, J46.B1, J46.B12, R45.1, R46.1, SHLD22.1
GND23: J47.1, J48.A1, J48.A12, J48.B1, J48.B12, R47.1, R48.1, SHLD23.1
GND24: J49.1, J50.A1, J50.A12, J50.B1, J50.B12, R49.1, R50.1, SHLD24.1
GND25: J51.1, J52.A1, J52.A12, J52.B1, J52.B12, R51.1, R52.1, SHLD25.1
GND26: J53.1, J54.A1, J54.A12, J54.B1, J54.B12, R53.1, R54.1, SHLD26.1
GND27: J55.1, J56.A1, J56.A12, J56.B1, J56.B12, R55.1, R56.1, SHLD27.1
GND28: J57.1, J58.A1, J58.A12, J58.B1, J58.B12, R57.1, R58.1, SHLD28.1
GND29: J59.1, J60.A1, J60.A12, J60.B1, J60.B12, R59.1, R60.1, SHLD29.1
GND30: J61.1, J62.A1, J62.A12, J62.B1, J62.B12, R61.1, R62.1, SHLD30.1
GND31: J63.1, J64.A1, J64.A12, J64.B1, J64.B12, R63.1, R64.1, SHLD31.1
GND32: J65.1, J66.A1, J66.A12, J66.B1, J66.B12, R65.1, R66.1, SHLD32.1
GND33: J67.1, J68.A1, J68.A12, J68.B1, J68.B12, R67.1, R68.1, SHLD33.1
GND34: J69.1, J70.A1, J70.A12, J70.B1, J70.B12, R69.1, R70.1, SHLD34.1
GND35: J71.1, J72.A1, J72.A12, J72.B1, J72.B12, R71.1, R72.1, SHLD35.1
GND36: J73.1, J74.A1, J74.A12, J74.B1, J74.B12, R73.1, R74.1, SHLD36.1
GND37: J75.1, J76.A1, J76.A12, J76.B1, J76.B12, R75.1, R76.1, SHLD37.1
GND38: J77.1, J78.A1, J78.A12, J78.B1, J78.B12, R77.1, R78.1, SHLD38.1
GND39: J79.1, J80.A1, J80.A12, J80.B1, J80.B12, R79.1, R80.1, SHLD39.1
GND40: J81.1, J82.A1, J82.A12, J82.B1, J82.B12, R81.1, R82.1, SHLD40.1
GND41: J83.1, J84.A1, J84.A12, J84.B1, J84.B12, R83.1, R84.1, SHLD41.1
GND42: J85.1, J86.A1, J86.A12, J86.B1, J86.B12, R85.1, R86.1, SHLD42.1
GND43: J87.1, J88.A1, J88.A12, J88.B1, J88.B12, R87.1, R88.1, SHLD43.1
GND44: J89.1, J90.A1, J90.A12, J90.B1, J90.B12, R89.1, R90.1, SHLD44.1
GND45: J91.1, J92.A1, J92.A12, J92.B1, J92.B12, R91.1, R92.1, SHLD45.1
GND46: J93.1, J94.A1, J94.A12, J94.B1, J94.B12, R93.1, R94.1, SHLD46.1
GND47: J95.1, J96.A1, J96.A12, J96.B1, J96.B12, R95.1, R96.1, SHLD47.1
GND48: J97.1, J98.A1, J98.A12, J98.B1, J98.B12, R97.1, R98.1, SHLD48.1
GND49: J99.1, J100.A1, J100.A12, J100.B1, J100.B12, R99.1, R100.1, SHLD49.1
GND50: J101.1, J102.A1, J102.A12, J102.B1, J102.B12, R101.1, R102.1, SHLD50.1
GND51: J103.1, J104.A1, J104.A12, J104.B1, J104.B12, R103.1, R104.1, SHLD51.1
GND52: J105.1, J106.A1, J106.A12, J106.B1, J106.B12, R105.1, R106.1, SHLD52.1
GND53: J107.1, J108.A1, J108.A12, J108.B1, J108.B12, R107.1, R108.1, SHLD53.1
GND54: J109.1, J110.A1, J110.A12, J110.B1, J110.B12, R109.1, R110.1, SHLD54.1
GND55: J111.1, J112.A1, J112.A12, J112.B1, J112.B12, R111.1, R112.1, SHLD55.1
GND56: J113.1, J114.A1, J114.A12, J114.B1, J114.B12, R113.1, R114.1, SHLD56.1
GND57: J115.1, J116.A1, J116.A12, J116.B1, J116.B12, R115.1, R116.1, SHLD57.1
GND58: J117.1, J118.A1, J118.A12, J118.B1, J118.B12, R117.1, R118.1, SHLD58.1
GND59: J119.1, J120.A1, J120.A12, J120.B1, J120.B12, R119.1, R120.1, SHLD59.1
GND60: J121.1, J122.A1, J122.A12, J122.B1, J122.B12, R121.1, R122.1, SHLD60.1
GND61: J123.1, J124.A1, J124.A12, J124.B1, J124.B12, R123.1, R124.1, SHLD61.1
GND62: J125.1, J126.A1, J126.A12, J126.B1, J126.B12, R125.1, R126.1, SHLD62.1
GND63: J127.1, J128.A1, J128.A12, J128.B1, J128.B12, R127.1, R128.1, SHLD63.1
GND64: J129.1, J130.A1, J130.A12, J130.B1, J130.B12, R129.1, R130.1, SHLD64.1
GND65: J131.1, J132.A1, J132.A12, J132.B1, J132.B12, R131.1, R132.1, SHLD65.1
GND66: J133.1, J134.A1, J134.A12, J134.B1, J134.B12, R133.1, R134.1, SHLD66.1
GND67: J135.1, J136.A1, J136.A12, J136.B1, J136.B12, R135.1, R136.1, SHLD67.1
GND68: J137.1, J138.A1, J138.A12, J138.B1, J138.B12, R137.1, R138.1, SHLD68.1
GND69: J139.1, J140.A1, J140.A12, J140.B1, J140.B12, R139.1, R140.1, SHLD69.1
SHLD: J1.2, J2.SHLD1, J2.SHLD2, J2.SHLD3, J2.SHLD4, SHLD.2
SHLD1: J3.2, J4.SHLD1, J4.SHLD2, J4.SHLD3, J4.SHLD4, SHLD1.2
SHLD2: J5.2, J6.SHLD1, J6.SHLD2, J6.SHLD3, J6.SHLD4, SHLD2.2
SHLD3: J7.2, J8.SHLD1, J8.SHLD2, J8.SHLD3, J8.SHLD4, SHLD3.2
SHLD4: J9.2, J10.SHLD1, J10.SHLD2, J10.SHLD3, J10.SHLD4, SHLD4.2
SHLD5: J11.2, J12.SHLD1, J12.SHLD2, J12.SHLD3, J12.SHLD4, SHLD5.2
SHLD6: J13.2, J14.SHLD1, J14.SHLD2, J14.SHLD3, J14.SHLD4, SHLD6.2
SHLD7: J15.2, J16.SHLD1, J16.SHLD2, J16.SHLD3, J16.SHLD4, SHLD7.2
SHLD8: J17.2, J18.SHLD1, J18.SHLD2, J18.SHLD3, J18.SHLD4, SHLD8.2
SHLD9: J19.2, J20.SHLD1, J20.SHLD2, J20.SHLD3, J20.SHLD4, SHLD9.2
SHLD10: J21.2, J22.SHLD1, J22.SHLD2, J22.SHLD3, J22.SHLD4, SHLD10.2
SHLD11: J23.2, J24.SHLD1, J24.SHLD2, J24.SHLD3, J24.SHLD4, SHLD11.2
SHLD12: J25.2, J26.SHLD1, J26.SHLD2, J26.SHLD3, J26.SHLD4, SHLD12.2
SHLD13: J27.2, J28.SHLD1, J28.SHLD2, J28.SHLD3, J28.SHLD4, SHLD13.2
SHLD14: J29.2, J30.SHLD1, J30.SHLD2, J30.SHLD3, J30.SHLD4, SHLD14.2
SHLD15: J31.2, J32.SHLD1, J32.SHLD2, J32.SHLD3, J32.SHLD4, SHLD15.2
SHLD16: J33.2, J34.SHLD1, J34.SHLD2, J34.SHLD3, J34.SHLD4, SHLD16.2
SHLD17: J35.2, J36.SHLD1, J36.SHLD2, J36.SHLD3, J36.SHLD4, SHLD17.2
SHLD18: J37.2, J38.SHLD1, J38.SHLD2, J38.SHLD3, J38.SHLD4, SHLD18.2
SHLD19: J39.2, J40.SHLD1, J40.SHLD2, J40.SHLD3, J40.SHLD4, SHLD19.2
SHLD20: J41.2, J42.SHLD1, J42.SHLD2, J42.SHLD3, J42.SHLD4, SHLD20.2
SHLD21: J43.2, J44.SHLD1, J44.SHLD2, J44.SHLD3, J44.SHLD4, SHLD21.2
SHLD22: J45.2, J46.SHLD1, J46.SHLD2, J46.SHLD3, J46.SHLD4, SHLD22.2
SHLD23: J47.2, J48.SHLD1, J48.SHLD2, J48.SHLD3, J48.SHLD4, SHLD23.2
SHLD24: J49.2, J50.SHLD1, J50.SHLD2, J50.SHLD3, J50.SHLD4, SHLD24.2
SHLD25: J51.2, J52.SHLD1, J52.SHLD2, J52.SHLD3, J52.SHLD4, SHLD25.2
SHLD26: J53.2, J54.SHLD1, J54.SHLD2, J54.SHLD3, J54.SHLD4, SHLD26.2
SHLD27: J55.2, J56.SHLD1, J56.SHLD2, J56.SHLD3, J56.SHLD4, SHLD27.2
SHLD28: J57.2, J58.SHLD1, J58.SHLD2, J58.SHLD3, J58.SHLD4, SHLD28.2
SHLD29: J59.2, J60.SHLD1, J60.SHLD2, J60.SHLD3, J60.SHLD4, SHLD29.2
SHLD30: J61.2, J62.SHLD1, J62.SHLD2, J62.SHLD3, J62.SHLD4, SHLD30.2
SHLD31: J63.2, J64.SHLD1, J64.SHLD2, J64.SHLD3, J64.SHLD4, SHLD31.2
SHLD32: J65.2, J66.SHLD1, J66.SHLD2, J66.SHLD3, J66.SHLD4, SHLD32.2
SHLD33: J67.2, J68.SHLD1, J68.SHLD2, J68.SHLD3, J68.SHLD4, SHLD33.2
SHLD34: J69.2, J70.SHLD1, J70.SHLD2, J70.SHLD3, J70.SHLD4, SHLD34.2
SHLD35: J71.2, J72.SHLD1, J72.SHLD2, J72.SHLD3, J72.SHLD4, SHLD35.2
SHLD36: J73.2, J74.SHLD1, J74.SHLD2, J74.SHLD3, J74.SHLD4, SHLD36.2
SHLD37: J75.2, J76.SHLD1, J76.SHLD2, J76.SHLD3, J76.SHLD4, SHLD37.2
SHLD38: J77.2, J78.SHLD1, J78.SHLD2, J78.SHLD3, J78.SHLD4, SHLD38.2
SHLD39: J79.2, J80.SHLD1, J80.SHLD2, J80.SHLD3, J80.SHLD4, SHLD39.2
SHLD40: J81.2, J82.SHLD1, J82.SHLD2, J82.SHLD3, J82.SHLD4, SHLD40.2
SHLD41: J83.2, J84.SHLD1, J84.SHLD2, J84.SHLD3, J84.SHLD4, SHLD41.2
SHLD42: J85.2, J86.SHLD1, J86.SHLD2, J86.SHLD3, J86.SHLD4, SHLD42.2
SHLD43: J87.2, J88.SHLD1, J88.SHLD2, J88.SHLD3, J88.SHLD4, SHLD43.2
SHLD44: J89.2, J90.SHLD1, J90.SHLD2, J90.SHLD3, J90.SHLD4, SHLD44.2
SHLD45: J91.2, J92.SHLD1, J92.SHLD2, J92.SHLD3, J92.SHLD4, SHLD45.2
SHLD46: J93.2, J94.SHLD1, J94.SHLD2, J94.SHLD3, J94.SHLD4, SHLD46.2
SHLD47: J95.2, J96.SHLD1, J96.SHLD2, J96.SHLD3, J96.SHLD4, SHLD47.2
SHLD48: J97.2, J98.SHLD1, J98.SHLD2, J98.SHLD3, J98.SHLD4, SHLD48.2
SHLD49: J99.2, J100.SHLD1, J100.SHLD2, J100.SHLD3, J100.SHLD4, SHLD49.2
SHLD50: J101.2, J102.SHLD1, J102.SHLD2, J102.SHLD3, J102.SHLD4, SHLD50.2
SHLD51: J103.2, J104.SHLD1, J104.SHLD2, J104.SHLD3, J104.SHLD4, SHLD51.2
SHLD52: J105.2, J106.SHLD1, J106.SHLD2, J106.SHLD3, J106.SHLD4, SHLD52.2
SHLD53: J107.2, J108.SHLD1, J108.SHLD2, J108.SHLD3, J108.SHLD4, SHLD53.2
SHLD54: J109.2, J110.SHLD1, J110.SHLD2, J110.SHLD3, J110.SHLD4, SHLD54.2
SHLD55: J111.2, J112.SHLD1, J112.SHLD2, J112.SHLD3, J112.SHLD4, SHLD55.2
SHLD56: J113.2, J114.SHLD1, J114.SHLD2, J114.SHLD3, J114.SHLD4, SHLD56.2
SHLD57: J115.2, J116.SHLD1, J116.SHLD2, J116.SHLD3, J116.SHLD4, SHLD57.2
SHLD58: J117.2, J118.SHLD1, J118.SHLD2, J118.SHLD3, J118.SHLD4, SHLD58.2
SHLD59: J119.2, J120.SHLD1, J120.SHLD2, J120.SHLD3, J120.SHLD4, SHLD59.2
SHLD60: J121.2, J122.SHLD1, J122.SHLD2, J122.SHLD3, J122.SHLD4, SHLD60.2
SHLD61: J123.2, J124.SHLD1, J124.SHLD2, J124.SHLD3, J124.SHLD4, SHLD61.2
SHLD62: J125.2, J126.SHLD1, J126.SHLD2, J126.SHLD3, J126.SHLD4, SHLD62.2
SHLD63: J127.2, J128.SHLD1, J128.SHLD2, J128.SHLD3, J128.SHLD4, SHLD63.2
SHLD64: J129.2, J130.SHLD1, J130.SHLD2, J130.SHLD3, J130.SHLD4, SHLD64.2
SHLD65: J131.2, J132.SHLD1, J132.SHLD2, J132.SHLD3, J132.SHLD4, SHLD65.2
SHLD66: J133.2, J134.SHLD1, J134.SHLD2, J134.SHLD3, J134.SHLD4, SHLD66.2
SHLD67: J135.2, J136.SHLD1, J136.SHLD2, J136.SHLD3, J136.SHLD4, SHLD67.2
SHLD68: J137.2, J138.SHLD1, J138.SHLD2, J138.SHLD3, J138.SHLD4, SHLD68.2
SHLD69: J139.2, J140.SHLD1, J140.SHLD2, J140.SHLD3, J140.SHLD4, SHLD69.2
VBUS: J1.7, J2.A4, J2.A9, J2.B4, J2.B9
VBUS1: J3.7, J4.A4, J4.A9, J4.B4, J4.B9
VBUS2: J5.7, J6.A4, J6.A9, J6.B4, J6.B9
VBUS3: J7.7, J8.A4, J8.A9, J8.B4, J8.B9
VBUS4: J9.7, J10.A4, J10.A9, J10.B4, J10.B9
VBUS5: J11.7, J12.A4, J12.A9, J12.B4, J12.B9
VBUS6: J13.7, J14.A4, J14.A9, J14.B4, J14.B9
VBUS7: J15.7, J16.A4, J16.A9, J16.B4, J16.B9
VBUS8: J17.7, J18.A4, J18.A9, J18.B4, J18.B9
VBUS9: J19.7, J20.A4, J20.A9, J20.B4, J20.B9
VBUS10: J21.7, J22.A4, J22.A9, J22.B4, J22.B9
VBUS11: J23.7, J24.A4, J24.A9, J24.B4, J24.B9
VBUS12: J25.7, J26.A4, J26.A9, J26.B4, J26.B9
VBUS13: J27.7, J28.A4, J28.A9, J28.B4, J28.B9
VBUS14: J29.7, J30.A4, J30.A9, J30.B4, J30.B9
VBUS15: J31.7, J32.A4, J32.A9, J32.B4, J32.B9
VBUS16: J33.7, J34.A4, J34.A9, J34.B4, J34.B9
VBUS17: J35.7, J36.A4, J36.A9, J36.B4, J36.B9
VBUS18: J37.7, J38.A4, J38.A9, J38.B4, J38.B9
VBUS19: J39.7, J40.A4, J40.A9, J40.B4, J40.B9
VBUS20: J41.7, J42.A4, J42.A9, J42.B4, J42.B9
VBUS21: J43.7, J44.A4, J44.A9, J44.B4, J44.B9
VBUS22: J45.7, J46.A4, J46.A9, J46.B4, J46.B9
VBUS23: J47.7, J48.A4, J48.A9, J48.B4, J48.B9
VBUS24: J49.7, J50.A4, J50.A9, J50.B4, J50.B9
VBUS25: J51.7, J52.A4, J52.A9, J52.B4, J52.B9
VBUS26: J53.7, J54.A4, J54.A9, J54.B4, J54.B9
VBUS27: J55.7, J56.A4, J56.A9, J56.B4, J56.B9
VBUS28: J57.7, J58.A4, J58.A9, J58.B4, J58.B9
VBUS29: J59.7, J60.A4, J60.A9, J60.B4, J60.B9
VBUS30: J61.7, J62.A4, J62.A9, J62.B4, J62.B9
VBUS31: J63.7, J64.A4, J64.A9, J64.B4, J64.B9
VBUS32: J65.7, J66.A4, J66.A9, J66.B4, J66.B9
VBUS33: J67.7, J68.A4, J68.A9, J68.B4, J68.B9
VBUS34: J69.7, J70.A4, J70.A9, J70.B4, J70.B9
VBUS35: J71.7, J72.A4, J72.A9, J72.B4, J72.B9
VBUS36: J73.7, J74.A4, J74.A9, J74.B4, J74.B9
VBUS37: J75.7, J76.A4, J76.A9, J76.B4, J76.B9
VBUS38: J77.7, J78.A4, J78.A9, J78.B4, J78.B9
VBUS39: J79.7, J80.A4, J80.A9, J80.B4, J80.B9
VBUS40: J81.7, J82.A4, J82.A9, J82.B4, J82.B9
VBUS41: J83.7, J84.A4, J84.A9, J84.B4, J84.B9
VBUS42: J85.7, J86.A4, J86.A9, J86.B4, J86.B9
VBUS43: J87.7, J88.A4, J88.A9, J88.B4, J88.B9
VBUS44: J89.7, J90.A4, J90.A9, J90.B4, J90.B9
VBUS45: J91.7, J92.A4, J92.A9, J92.B4, J92.B9
VBUS46: J93.7, J94.A4, J94.A9, J94.B4, J94.B9
VBUS47: J95.7, J96.A4, J96.A9, J96.B4, J96.B9
VBUS48: J97.7, J98.A4, J98.A9, J98.B4, J98.B9
VBUS49: J99.7, J100.A4, J100.A9, J100.B4, J100.B9
VBUS50: J101.7, J102.A4, J102.A9, J102.B4, J102.B9
VBUS51: J103.7, J104.A4, J104.A9, J104.B4, J104.B9
VBUS52: J105.7, J106.A4, J106.A9, J106.B4, J106.B9
VBUS53: J107.7, J108.A4, J108.A9, J108.B4, J108.B9
VBUS54: J109.7, J110.A4, J110.A9, J110.B4, J110.B9
VBUS55: J111.7, J112.A4, J112.A9, J112.B4, J112.B9
VBUS56: J113.7, J114.A4, J114.A9, J114.B4, J114.B9
VBUS57: J115.7, J116.A4, J116.A9, J116.B4, J116.B9
VBUS58: J117.7, J118.A4, J118.A9, J118.B4, J118.B9
VBUS59: J119.7, J120.A4, J120.A9, J120.B4, J120.B9
VBUS60: J121.7, J122.A4, J122.A9, J122.B4, J122.B9
VBUS61: J123.7, J124.A4, J124.A9, J124.B4, J124.B9
VBUS62: J125.7, J126.A4, J126.A9, J126.B4, J126.B9
VBUS63: J127.7, J128.A4, J128.A9, J128.B4, J128.B9
VBUS64: J129.7, J130.A4, J130.A9, J130.B4, J130.B9
VBUS65: J131.7, J132.A4, J132.A9, J132.B4, J132.B9
VBUS66: J133.7, J134.A4, J134.A9, J134.B4, J134.B9
VBUS67: J135.7, J136.A4, J136.A9, J136.B4, J136.B9
VBUS68: J137.7, J138.A4, J138.A9, J138.B4, J138.B9
VBUS69: J139.7, J140.A4, J140.A9, J140.B4, J140.B9

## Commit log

2023-07-24 Initial upload of given files
    Files have been handed off and now uploaded in this file folder. The eagle files have the revision name now changed.
2023-07-26 Repo Restructure, Work to board
    Finished the new connector and the board layout; updates to schematic
2023-07-26 Ready for Protos Design Review
    Updated the README and the board/schematic files in preparation for the protos design review. The only schematic change was the comment and position of the aesthetics, and the board change was aesthe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
2023-07-28 PCB files ready for order
    Made updates to schematic and layout as per the design review - see design review document for more detailed information. Added gerber files and BOM files for PCB assembly at JLC.
2023-07-28 Uploaded BOM and Pick and Place files
    Uploaded the correct files for ordering boards with assembly for JLCPCB
2023-07-28 Updated panel and BOM files
    Adjusted for JLCPCBA panels
2023-07-31 Files adjusted for JLCPCBA ordering
    Finished up the panel files, BOM, and pick and place files for ordering. Returned board back to original used after trying some testing. Files have been ordered!
2023-08-11 Updates for larger panel size
    Updated the design to be a larger panel size for ordering new parts.
2023-09-19 Added correct files for ordering single units
    If JLCPCB has issues with more orders, then we will have them panelize it and order boards through that method.
2023-09-28 Update
    Add product information
    Update license and contributing template files
